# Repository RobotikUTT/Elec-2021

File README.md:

# Elec-2021
Reprise des cartes électroniques de l'année 2019 cette fois-ci sous Eagle.

TODOS: 
Changer MCP2515 par son modèle en SMD. /Fait

Relier les pins du header CAN. /Fait

Pas de crystal? /Bahsi

Chercher les dimensions du slot de la carte? /Fait

Changer les condos en SMD /...?

3-pin 5V, GND + I2C en plus? /Fait

Changer le R17, R16 en 0207 /Fait

Mettre les IRQ1 et IRQ2 dans le même header GPIO /Fait 

Changer le VDD sur l'Arduino /Fait

Changer le capa d'entrée sur les servos(peut être plus proche au servo) /Fait

Changer les VCC en VDD /..?

Module stepstick? /...?

2-4 de 12V, 6 de GND pins à rajouter /Fait

Relier le 2ème pin du bouton au GND /Fait

Remettre la répétition des résistances pour servos /Fait...?

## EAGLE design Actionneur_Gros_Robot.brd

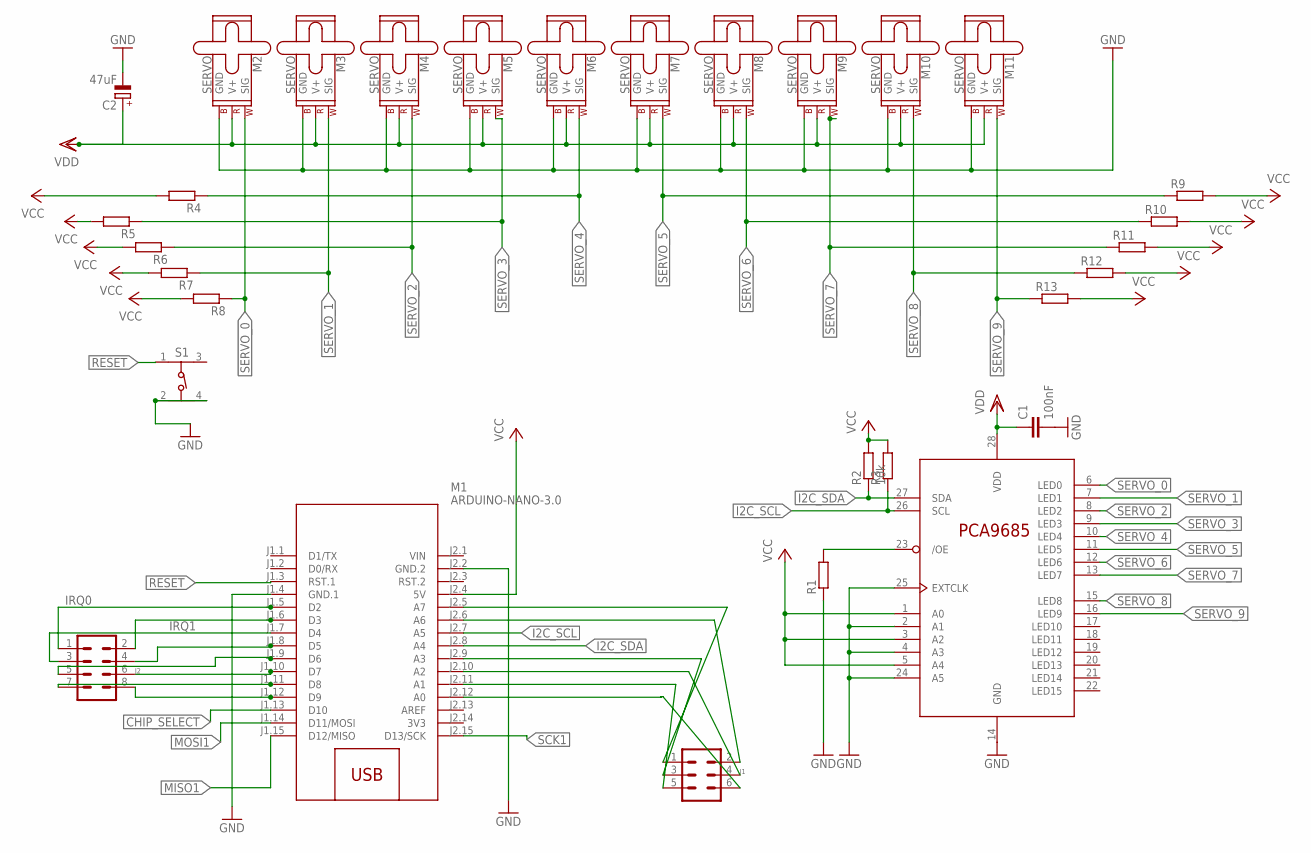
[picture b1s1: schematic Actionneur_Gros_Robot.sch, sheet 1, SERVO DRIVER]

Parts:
C1: 100nF; C025-025X050
C2: 47uF; E2,5-7
J1: MA03-2
J2: MA04-2
M1: ARDUINO-NANO-3.0
M2, M3, M4, M5, M6, M7, M8, M9, M10, M11: SERVO; 1X03
R1, R3, R4, R5, R6, R7, R8, R9, R10, R11, R12, R13: R-EU_0204/7; 0204/7
R2: 10k; 0204/7
S1: 430182043816
U$1: PCA9685PW; TSSOP28

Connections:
3V3: M1.J2.14 (3V3)
CHIP_SELECT: M1.J1.13 (D10); also elsewhere on the board
GND: C1.2, C2.-, M1.J1.4 (GND.1), M1.J2.2 (GND.2), M2.3 (GND), M3.3 (GND), M4.3 (GND), M5.3 (GND), M6.3 (GND), M7.3 (GND), M8.3 (GND), M9.3 (GND), M10.3 (GND), M11.3 (GND), R1.1, S1.2, S1.4, U$1.2 (A1), U$1.4 (A3), U$1.14 (GND), U$1.24 (A5), U$1.25 (EXTCLK); also elsewhere on the board
I2C_SCL: M1.J2.7 (A5), R3.1, U$1.26 (SCL); also elsewhere on the board
I2C_SDA: M1.J2.8 (A4), R2.1, U$1.27 (SDA); also elsewhere on the board
IRQ0: J2.1, M1.J1.5 (D2)
IRQ1: J2.2, M1.J1.6 (D3)
MISO1: M1.J1.15 (D12/MISO); also elsewhere on the board
MOSI1: M1.J1.14 (D11/MOSI); also elsewhere on the board
unnamed: R1.2, U$1.23 (/OE)
unnamed: J1.6, M1.J2.12 (A0)
unnamed: J1.5, M1.J2.11 (A1)
unnamed: J1.3, M1.J2.9 (A3)
unnamed: J1.4, M1.J2.10 (A2)
unnamed: J1.2, M1.J2.6 (A6)
unnamed: J1.1, M1.J2.5 (A7)
unnamed: J2.8, M1.J1.12 (D9)
unnamed: J2.7, M1.J1.11 (D8)
unnamed: J2.6, M1.J1.10 (D7)
unnamed: J2.5, M1.J1.9 (D6)
unnamed: J2.4, M1.J1.8 (D5)
unnamed: J2.3, M1.J1.7 (D4)
RESET: M1.J1.3 (RST.1), S1.1; also elsewhere on the board
SCK1: M1.J2.15 (D13/SCK); also elsewhere on the board
SERVO_0: M2.1 (SIG), R8.1, U$1.6 (LED0)
SERVO_1: M3.1 (SIG), R7.1, U$1.7 (LED1)
SERVO_2: M4.1 (SIG), R6.1, U$1.8 (LED2)
SERVO_3: M5.1 (SIG), R5.1, U$1.9 (LED3)
SERVO_4: M6.1 (SIG), R4.1, U$1.10 (LED4)
SERVO_5: M7.1 (SIG), R9.1, U$1.11 (LED5)
SERVO_6: M8.1 (SIG), R10.1, U$1.12 (LED6)
SERVO_7: M9.1 (SIG), R11.1, U$1.13 (LED7)
SERVO_8: M10.1 (SIG), R12.1, U$1.15 (LED8)
SERVO_9: M11.1 (SIG), R13.1, U$1.16 (LED9)
VCC: C1.1, M1.J2.4 (5V), R2.2, R3.2, R4.2, R5.2, R6.2, R7.2, R8.2, R9.2, R10.2, R11.2, R12.2, R13.2, U$1.1 (A0), U$1.3 (A2), U$1.5 (A4), U$1.28 (VDD); also elsewhere on the board
VDD: C2.+, M2.2 (V+), M3.2 (V+), M4.2 (V+), M5.2 (V+), M6.2 (V+), M7.2 (V+), M8.2 (V+), M9.2 (V+), M10.2 (V+), M11.2 (V+); also elsewhere on the board
VIN: M1.J2.1 (VIN)

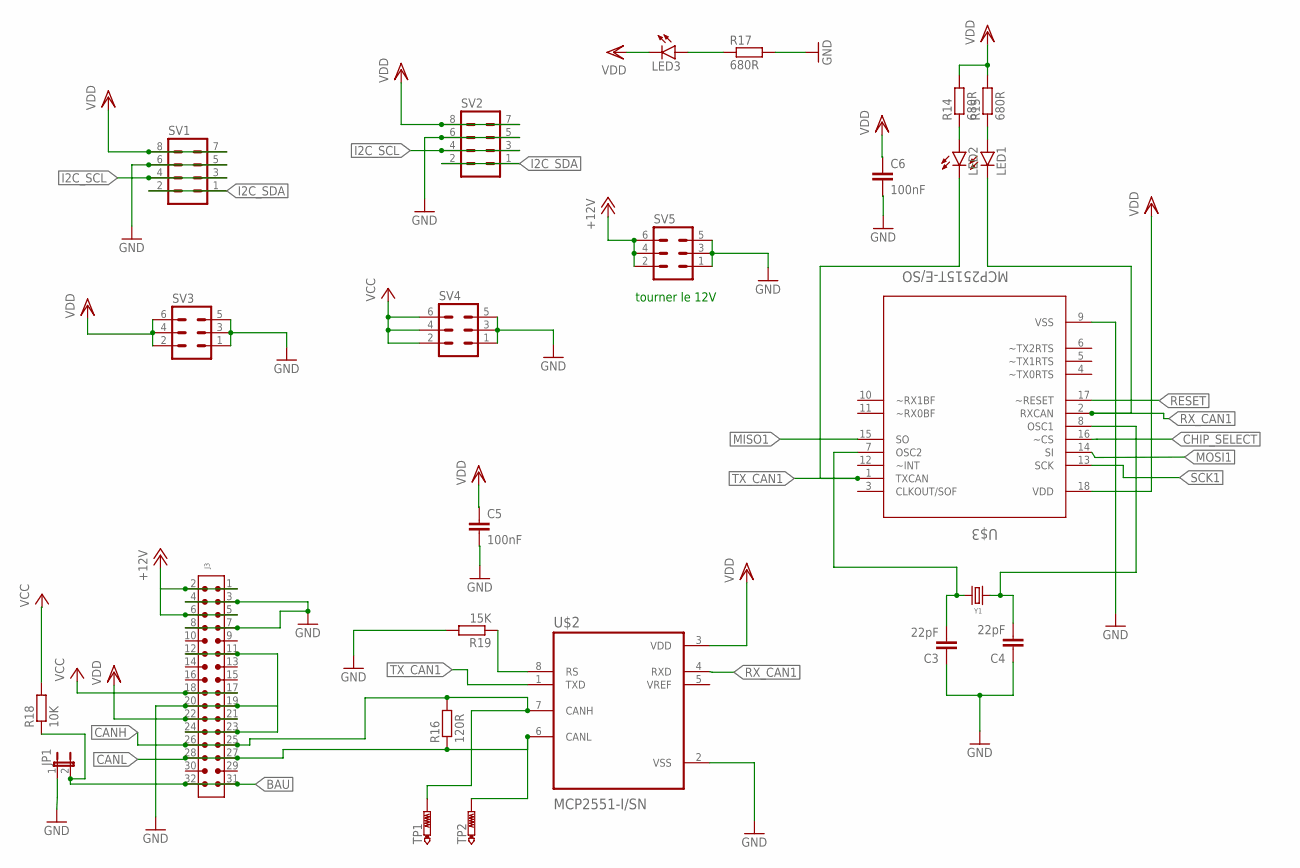
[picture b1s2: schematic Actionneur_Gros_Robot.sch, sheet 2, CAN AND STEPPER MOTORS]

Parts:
C3, C4: 22pF; C025-025X050
C5, C6: 100nF; C025-025X050
J3: 6130XX21021_61303221021; 61303221021
JP1: JP1E; JP1
LED1, LED2, LED3: LED3MM
R14, R15: 680R; 0207/10
R16: 120R; 0207/7
R17: 680R; 0207/7
R18: 10K; 0207/7
R19: 15K; 0207/7
SV1, SV2: MA04-2
SV3, SV4, SV5: MA03-2
TP1, TP2: PTR1PAD1-17; P1-17
U$2: MCP2551-I/SN; SOIC127P599X175-8N
U$3: MCP2515T-E/SO; SOIC127P1030X265-18N
Y1: 16MHz; HC49UP

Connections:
+12V: J3.1, J3.2, SV5.2, SV5.4, SV5.6
BAU: J3.31, J3.32, JP1.2, R18.1
CANH: J3.25, J3.26, R16.2, TP1.TP, U$2.7 (CANH)
CANL: J3.27, J3.28, R16.1, TP2.TP, U$2.6 (CANL)
CHIP_SELECT: U$3.16 (~CS); also elsewhere on the board
GND: C3.1, C4.1, C5.2, C6.2, J3.3, J3.4, J3.7, J3.8, J3.11, J3.12, J3.19, J3.20, J3.23, J3.24, JP1.1, R17.2, R19.2, SV1.5, SV1.6, SV2.5, SV2.6, SV3.1, SV3.3, SV3.5, SV4.1, SV4.3, SV4.5, SV5.1, SV5.3, SV5.5, U$2.2 (VSS), U$3.9 (VSS); also elsewhere on the board
I2C_SCL: SV1.3, SV1.4, SV2.3, SV2.4; also elsewhere on the board
I2C_SDA: SV1.1, SV1.2, SV2.1, SV2.2; also elsewhere on the board
MISO1: U$3.15 (SO); also elsewhere on the board
MOSI1: U$3.14 (SI); also elsewhere on the board
unnamed: J3.5, J3.6
unnamed: R19.1, U$2.8 (RS)
unnamed: LED1.A, R15.1
unnamed: LED2.A, R14.1
unnamed: LED3.A, R17.1
unnamed: C4.2, U$3.8 (OSC1), Y1.1
unnamed: C3.2, U$3.7 (OSC2), Y1.2
RESET: U$3.17 (~RESET); also elsewhere on the board
RX_CAN1: LED1.K (C), U$2.4 (RXD), U$3.2 (RXCAN)
SCK1: U$3.13 (SCK); also elsewhere on the board
TX_CAN1: LED2.K (C), U$2.1 (TXD), U$3.1 (TXCAN)
VCC: J3.17, J3.18, R18.2, SV4.2, SV4.4, SV4.6; also elsewhere on the board
VDD: C5.1, C6.1, J3.21, J3.22, LED3.K (C), R14.2, R15.2, SV1.7, SV1.8, SV2.7, SV2.8, SV3.2, SV3.4, SV3.6, U$2.3 (VDD), U$3.18 (VDD); also elsewhere on the board

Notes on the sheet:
tourner le 12V

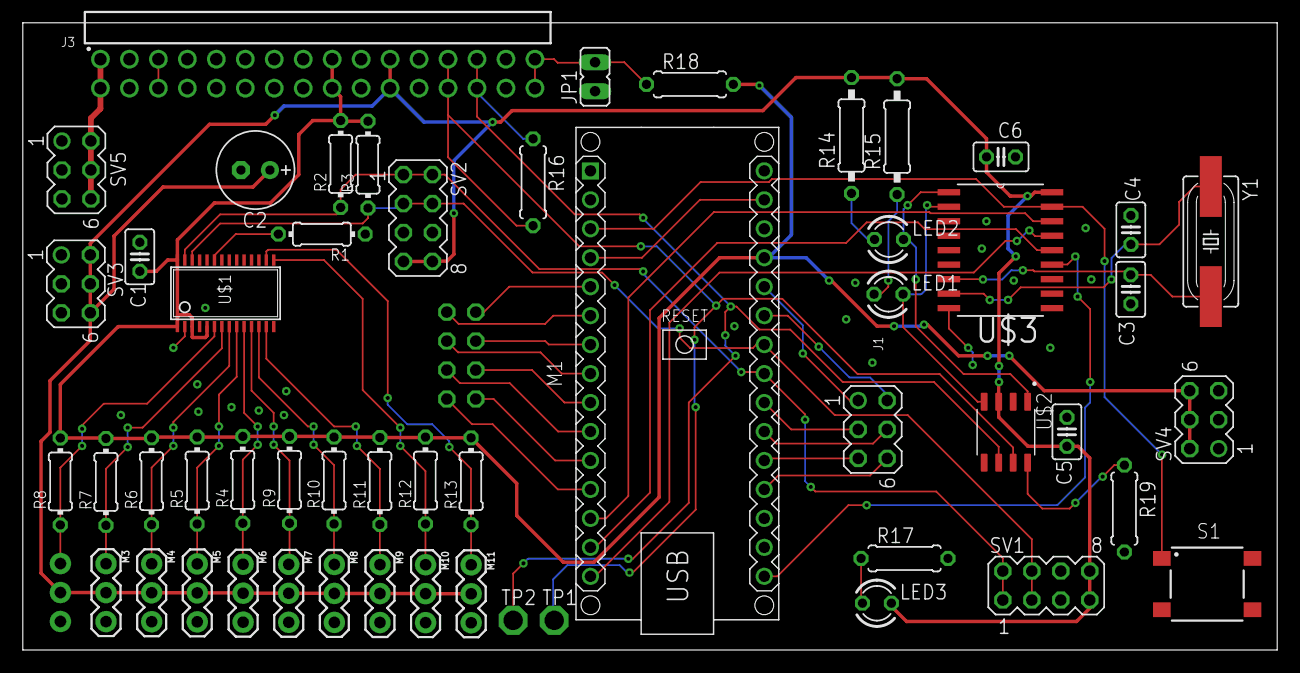
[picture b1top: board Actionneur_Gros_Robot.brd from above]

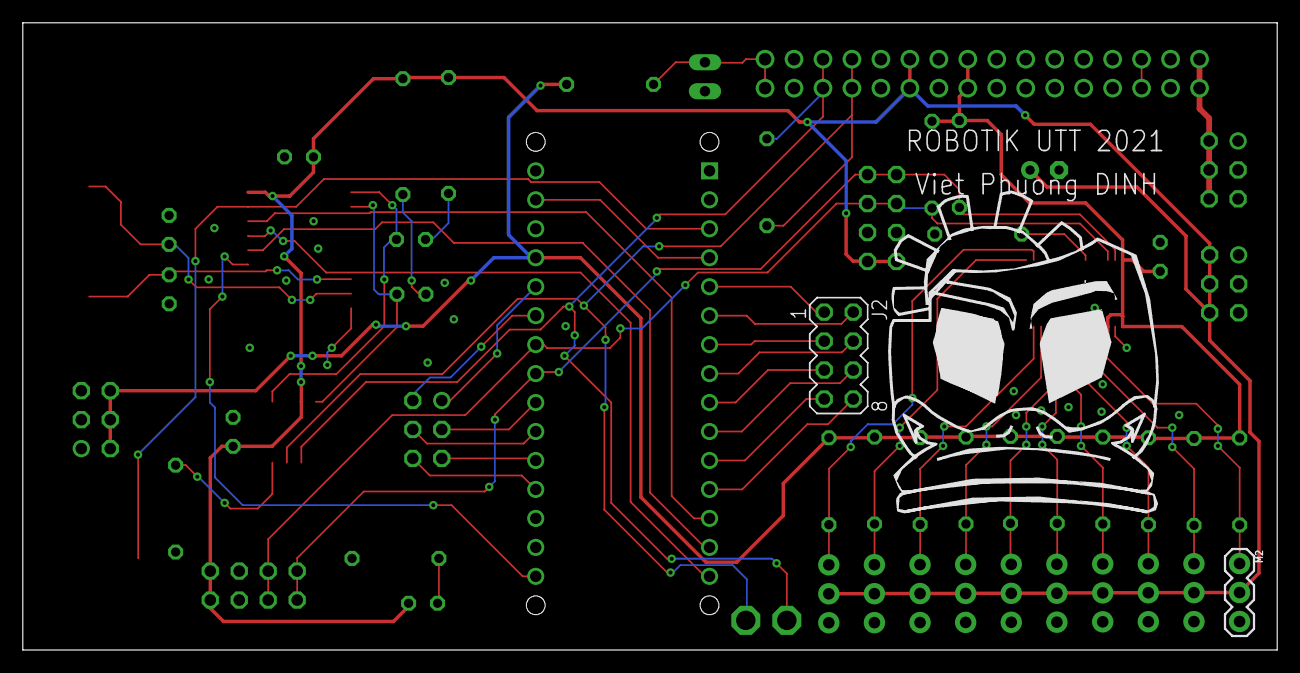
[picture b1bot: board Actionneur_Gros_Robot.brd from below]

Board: 2 copper layers, 110.0 x 55.0 mm, 55 parts (2 on the bottom side), 48 nets.

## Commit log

2021-02-23 Needed librairies for CAD models added. Mainframe actuators schematics available.
2021-03-25 added MCP2551 and MCP 2515
2021-05-11 Routing in progress
2021-05-11 En attente de révision
2021-05-22 v2 en cours de révision
2021-05-22 Ajout des pins 12V
2021-06-08 chgt schéma bouton d'arrêt d'urgence, condo 10 uF sur VDD
2021-06-10 Added CAM job
2021-06-16 ajout des fichiers gerber
2021-07-05 revA02
2021-07-06 revA2
2021-07-06 revA3
2021-07-06 Added testpins for CANH and CANL

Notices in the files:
parts and their libraries:
Wurth_Connectors_WR-PHD: Copyright: Würth Elektronik
diy-modules2: Released under the Creative Commons Attribution 4.0 International License: http://creativecommons.org/licenses/by/4.0
